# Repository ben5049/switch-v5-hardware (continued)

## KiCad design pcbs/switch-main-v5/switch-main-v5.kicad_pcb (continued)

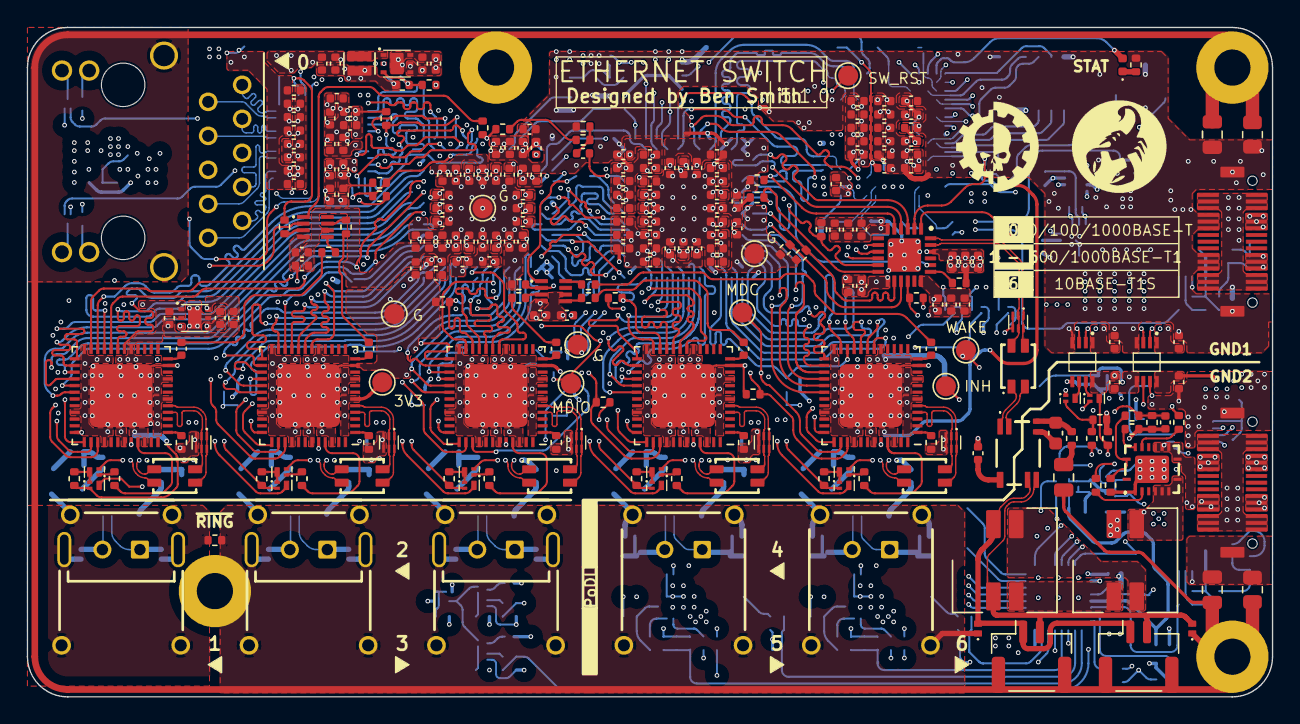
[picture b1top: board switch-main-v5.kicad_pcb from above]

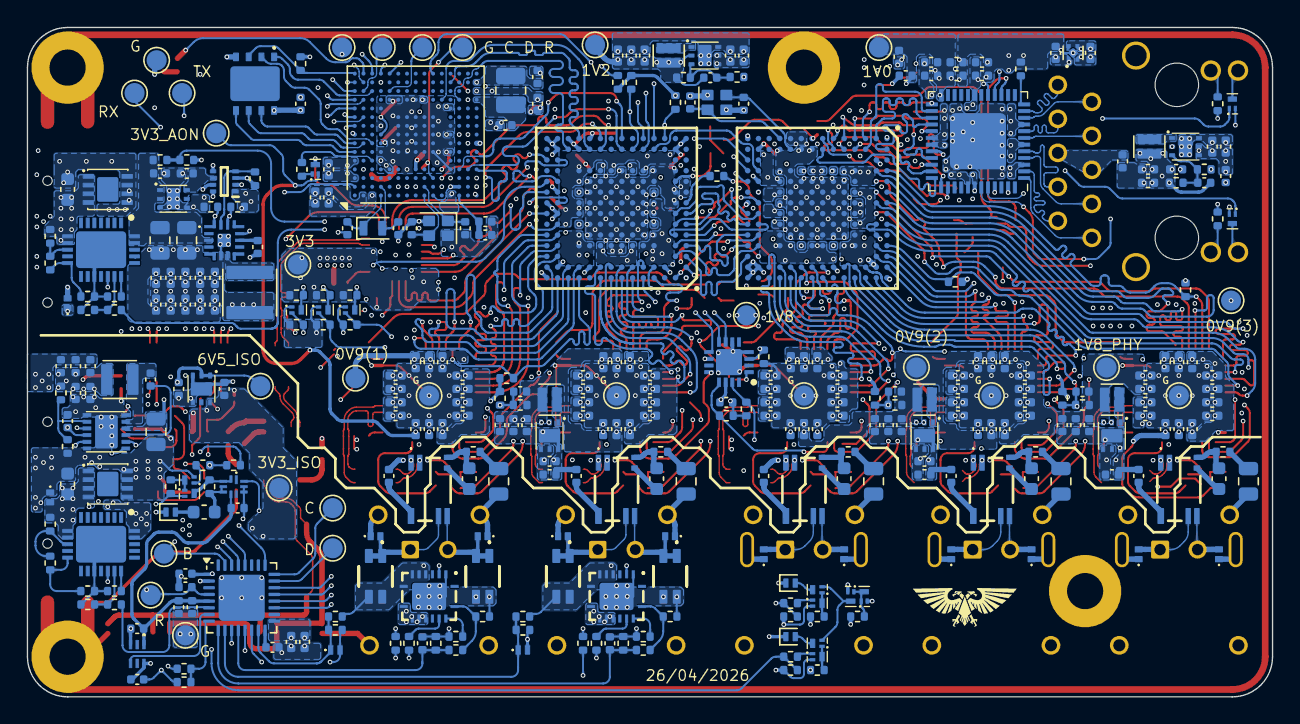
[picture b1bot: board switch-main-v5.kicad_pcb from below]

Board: 6 copper layers, 93.0 x 50.0 mm, 643 parts (373 on the bottom side), 396 nets.

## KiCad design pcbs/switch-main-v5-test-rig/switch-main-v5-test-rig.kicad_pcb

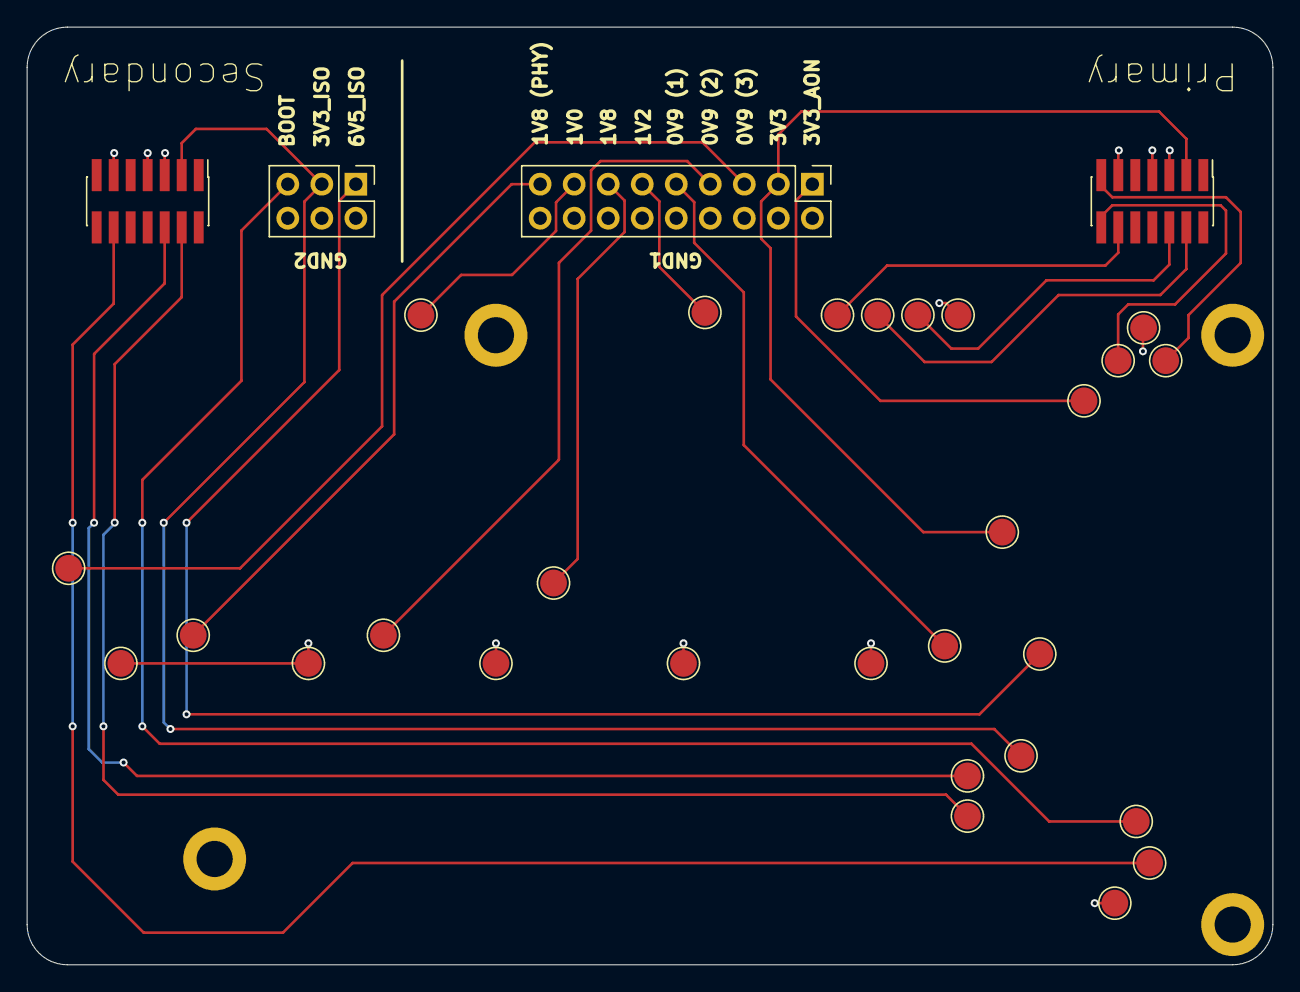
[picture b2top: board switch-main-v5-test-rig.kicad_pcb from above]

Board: 2 copper layers, 93.0 x 70.0 mm, 36 parts (0 on the bottom side), 22 nets.

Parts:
H101, H102, H103, H1001: MountingHole_Pad; MountingHole_2.7mm_M2.5_DIN965_Pad
J101, J104: Conn_ST_STDC14; PinHeader_2x07_P1.27mm_Vertical_SMD
J103: Conn_02x03_Odd_Even; PinHeader_2x03_P2.54mm_Vertical
J1001: Conn_02x09_Odd_Even; PinHeader_2x09_P2.54mm_Vertical
TP101, TP102, TP103, TP104, TP105, TP106, TP107, TP108, TP109, TP110, TP111, TP112, TP113, TP114, TP115, TP116, TP117, TP118, TP119, TP120, TP121, TP122, TP123, TP128, TP1001, TP1002, TP1003, TP1004: 2mm; TestPoint_Pad_D2.0mm

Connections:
+3V3: J101.3 (VCC), J1001.3, TP112.1
+3V3_ISO: J103.3, J104.3 (VCC), TP119.1
/0V9_1: J1001.9, TP116.1
/0V9_2: J1001.7, TP115.1
/0V9_3: J1001.5, TP114.1
/1V0: J1001.15, TP1003.1
/1V2: J1001.11, TP117.1
/1V8: J1001.13, TP113.1
/1V8_PHY: J1001.17, TP1004.1
/3V3_AON: J1001.1, TP111.1
/6V5_ISO: J103.1, TP118.1
GND1: J101.5 (GND), J101.7 (GND), J101.11 (GNDDetect), J1001.2, J1001.4, J1001.6, J1001.8, J1001.10, J1001.12, J1001.14, J1001.16, J1001.18, TP109.1, TP110.1, TP121.1, TP122.1, TP123.1, TP1001.1, TP1002.1
GND2: J103.2, J103.4, J103.6, J104.5 (GND), J104.7 (GND), J104.11 (GNDDetect), TP128.1
unnamed: J101.6 (JCLK/SWCLK), TP102.1
unnamed: J101.4 (JTMS/SWDIO), TP103.1
unnamed: J101.13 (VCP_RX), TP104.1
unnamed: J101.14 (VCP_TX), TP105.1
unnamed: J101.12 (~RST), TP101.1
unnamed: J103.5, TP120.1
unnamed: J104.6 (JCLK/SWCLK), TP107.1
unnamed: J104.4 (JTMS/SWDIO), TP108.1
unnamed: J104.12 (~RST), TP106.1

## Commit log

2025-10-09 Added WIP files & component library
2025-10-09 Updated gitignore
2025-10-11 MDIO multiplexing
2025-10-11 Started updating regulators for v5
2025-11-07 Updated component library
2025-11-07 Updated 1v0_buck_converter feedback resistors
2025-11-13 Changed main 3V3 regulator to 3A, added switch 2 crystal & other changes
2025-11-15 Moved components around and half routed 1000BASE-T PHY RGMII
2025-11-15 Routed and length matched inter-switch RGMII
2025-11-15 Routed switch 1 clocking
2025-11-16 PHY3 RGMII routed and length matched
2025-11-16 Routed and length matched 1000BASE-T PHY RGMII
2025-11-17 PHY 1 & 2 routing progress and passive placement
2025-11-17 Placed 1000BASE-T PHY decoupling capacitors
2025-11-19 Fixed test points
2025-11-19 Moved 0V9 regulators
2025-11-20 1V0 Rail done
2025-11-21 Updated README image
2025-11-21 Placed most remaining passives and test points
2025-11-23 All signals routed, need to do power still
2025-11-24 1V8 Power routed
2025-11-25 1V8_PHY Power routed
2025-11-26 0 Unrouted
2025-11-27 PHY 4 & 5 Length matching
2025-11-28 PHY 3 Length matching
2025-11-29 PHY 2 Length matching
2025-11-30 PHY 0 & 1 Length matching
2025-11-30 Fixed DRC issues and filleted outer layer traces
2025-12-01 Added PoDL indicator to silkscreen
2025-12-02 Added & updated media
2025-12-04 Made 10BASE-T1S PoDL tracks wider and untented certain viewers
2025-12-22 Added test rig PCB
2025-12-22 Changed primary side input current limit to 545mA (from 255mA which is less than the max possible load current of 326mA)
2025-12-23 Tidied schematic and PCB
2025-12-25 Updated crystal load capacitors
2025-12-27 Removed tenting from bottom side via pads
2025-12-29 Removed one switch crystal so both are now clocked from the same source and timestamps won't drift
2025-12-31 Component library updates
2026-01-01 Updated schematic comments
2026-01-03 Updated reference designators
2026-01-26 Minor schematic label update
2026-03-18 Move component library
2026-03-18 Cleaned up repository
2026-04-24 Fixed bug with IO voltage of connection between switch 0 and switch 1
2026-04-25 Added errata
2026-04-25 Documented fix for wrong IO voltage errata
2026-04-25 Tidied up PCB
